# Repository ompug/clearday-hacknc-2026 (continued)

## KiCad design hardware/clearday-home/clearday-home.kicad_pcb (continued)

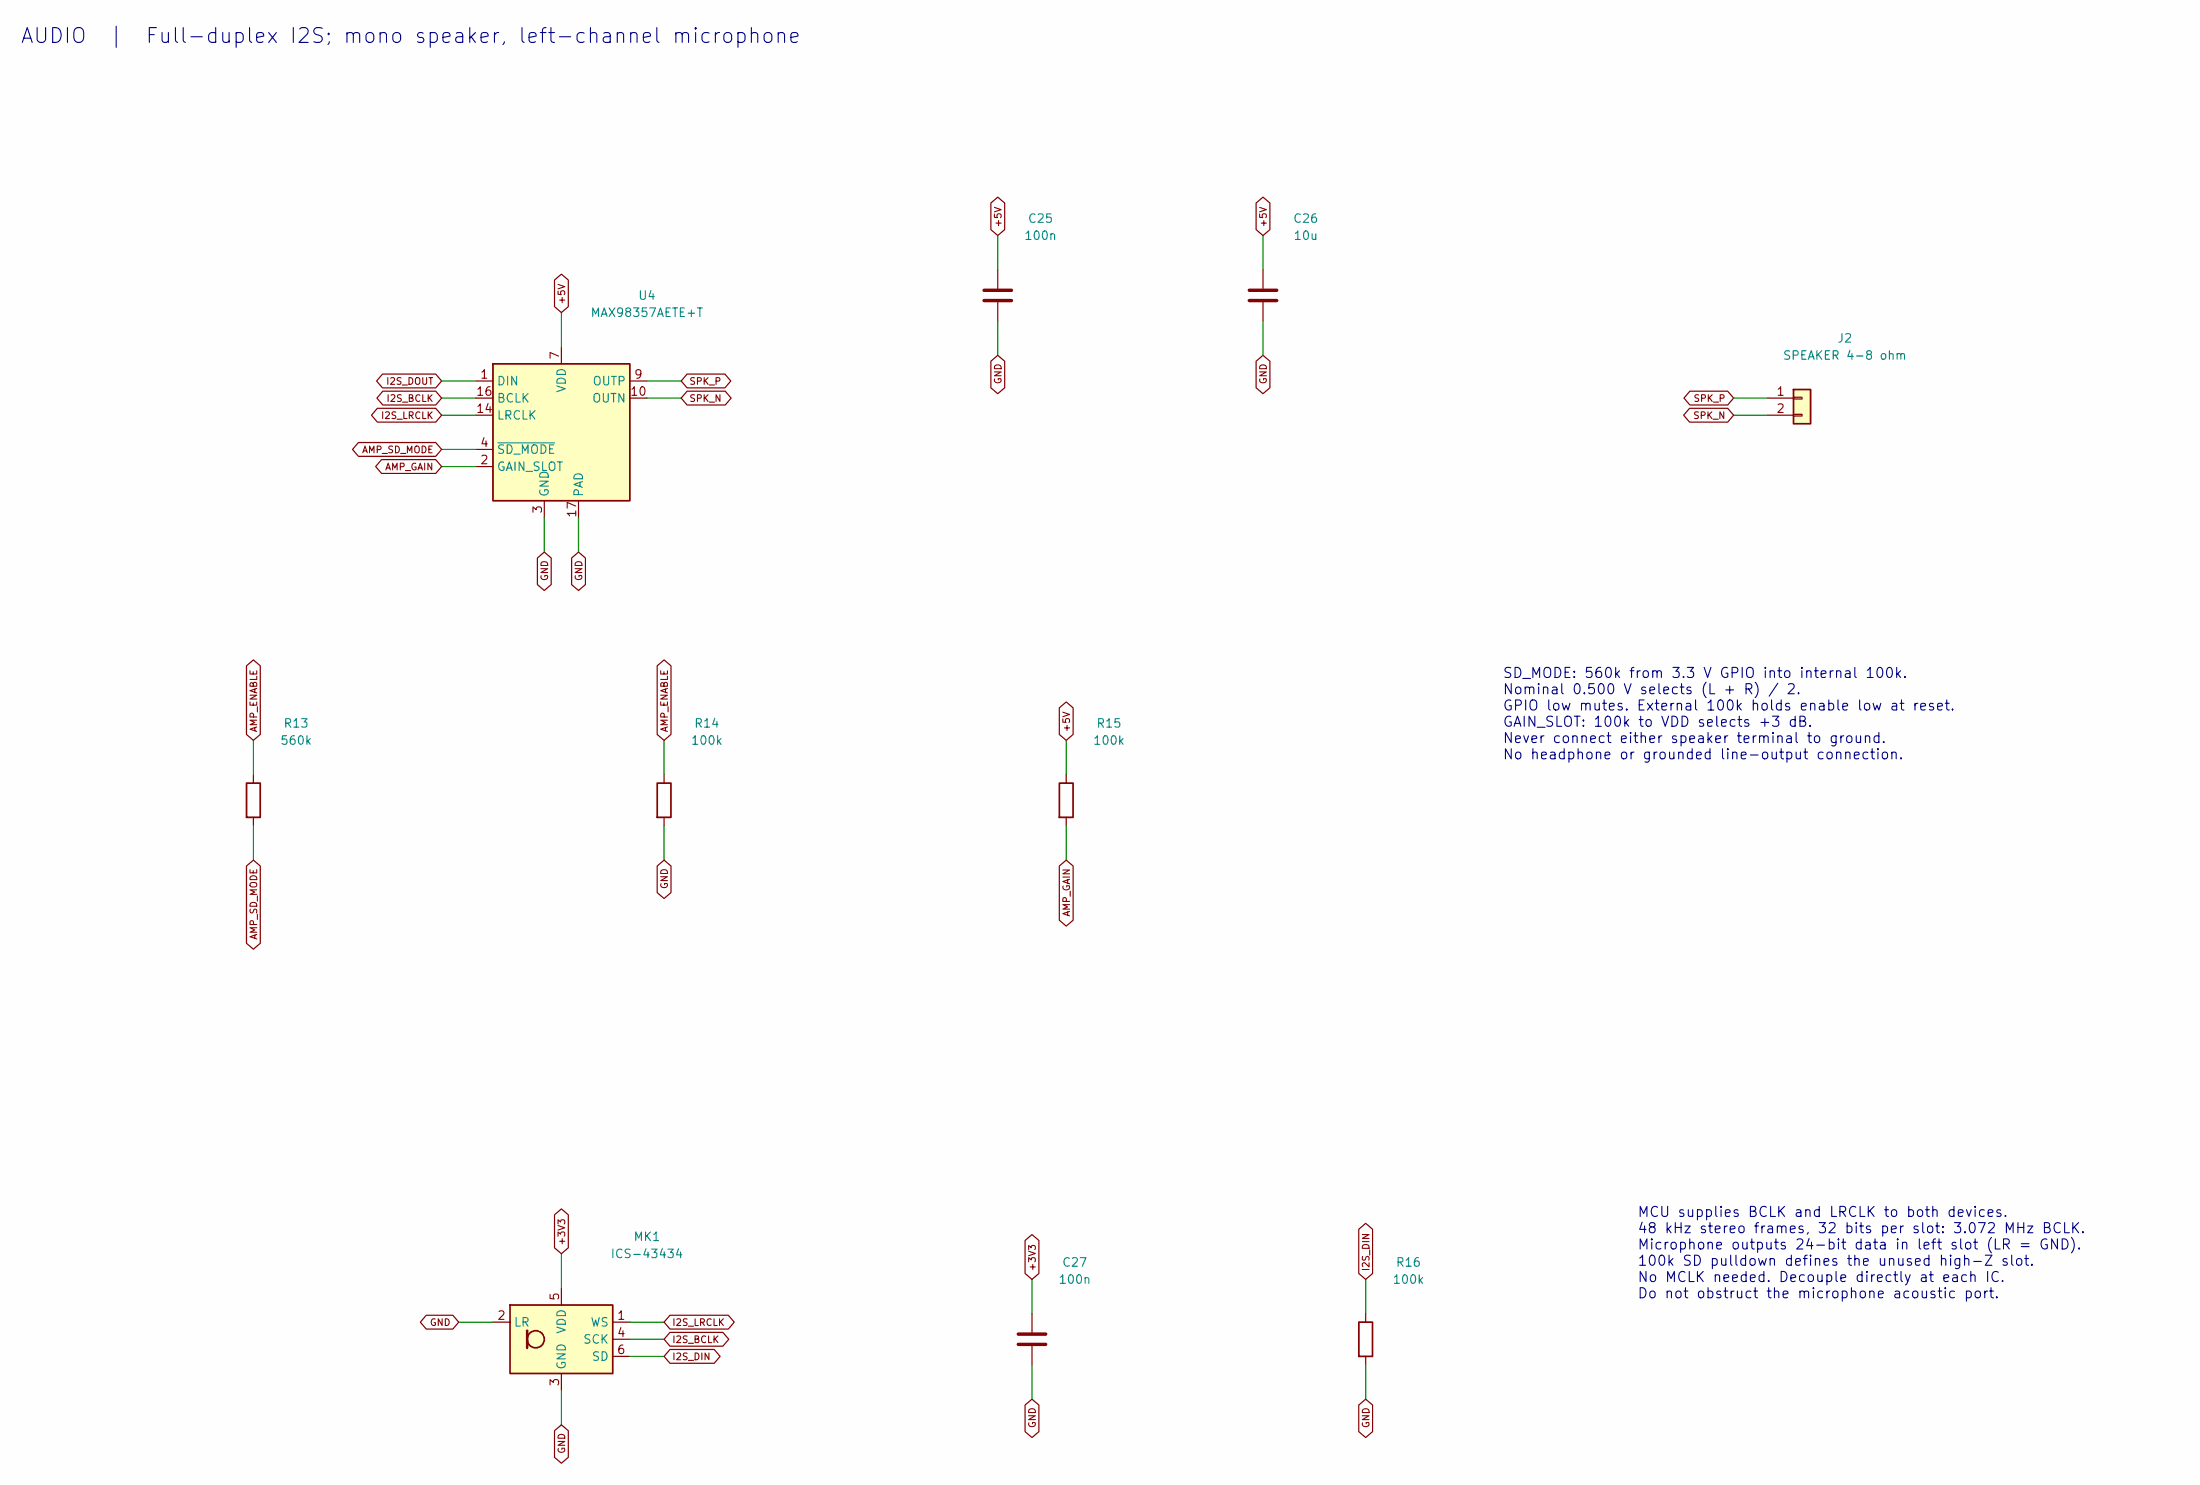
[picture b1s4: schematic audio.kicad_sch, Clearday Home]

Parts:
C25, C27: 100n; C_0603_1608Metric; MPN GRM188R71C104KA01D
C26: 10u; C_0805_2012Metric; MPN GRM21BR61A106KE19L
J2: SPEAKER 4-8 ohm; JST_PH_B2B-PH-K_1x02_P2.00mm_Vertical; MPN B2B-PH-K-S(LF)(SN)
MK1: ICS-43434; InvenSense_ICS-43434-6_3.5x2.65mm; MPN ICS-43434
R13: 560k; R_0603_1608Metric; MPN RC0603FR-07560KL
R14, R15, R16: 100k; R_0603_1608Metric; MPN RC0603FR-07100KL
U4: MAX98357AETE+T; TQFN-16-1EP_3x3mm_P0.5mm_EP1.23x1.23mm; MPN MAX98357AETE+T

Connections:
+3V3: C27.1, MK1.5 (VDD); also elsewhere on the board
+5V: C25.1, C26.1, R15.1, U4.7 (VDD), U4.8 (VDD); also elsewhere on the board
AMP_ENABLE: R13.1, R14.1; also elsewhere on the board
AMP_GAIN: R15.2, U4.2 (GAIN_SLOT)
AMP_SD_MODE: R13.2, U4.4 (~SD_MODE)
GND: C25.2, C26.2, C27.2, MK1.2 (LR), MK1.3 (GND), R14.2, R16.2, U4.3 (GND), U4.11 (GND), U4.15 (GND), U4.17 (PAD); also elsewhere on the board
I2S_BCLK: MK1.4 (SCK), U4.16 (BCLK); also elsewhere on the board
I2S_DIN: MK1.6 (SD), R16.1; also elsewhere on the board
I2S_DOUT: U4.1 (DIN); also elsewhere on the board
I2S_LRCLK: MK1.1 (WS), U4.14 (LRCLK); also elsewhere on the board
SPK_N: J2.2, U4.10 (OUTN)
SPK_P: J2.1, U4.9 (OUTP)

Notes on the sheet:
AUDIO | Full-duplex I2S; mono speaker, left-channel microphone
SD_MODE: 560k from 3.3 V GPIO into internal 100k. Nominal 0.500 V selects (L + R) / 2. GPIO low mutes. External 100k holds enable low at reset. GAIN_SLOT: 100k to VDD selects +3 dB. Never connect either speaker terminal to ground. No headphone or grounded line-output connection.
MCU supplies BCLK and LRCLK to both devices. 48 kHz stereo frames, 32 bits per slot: 3.072 MHz BCLK. Microphone outputs 24-bit data in left slot (LR = GND). 100k SD pulldown defines the unused high-Z slot. No MCLK needed. Decouple directly at each IC. Do not obstruct the microphone acoustic port.

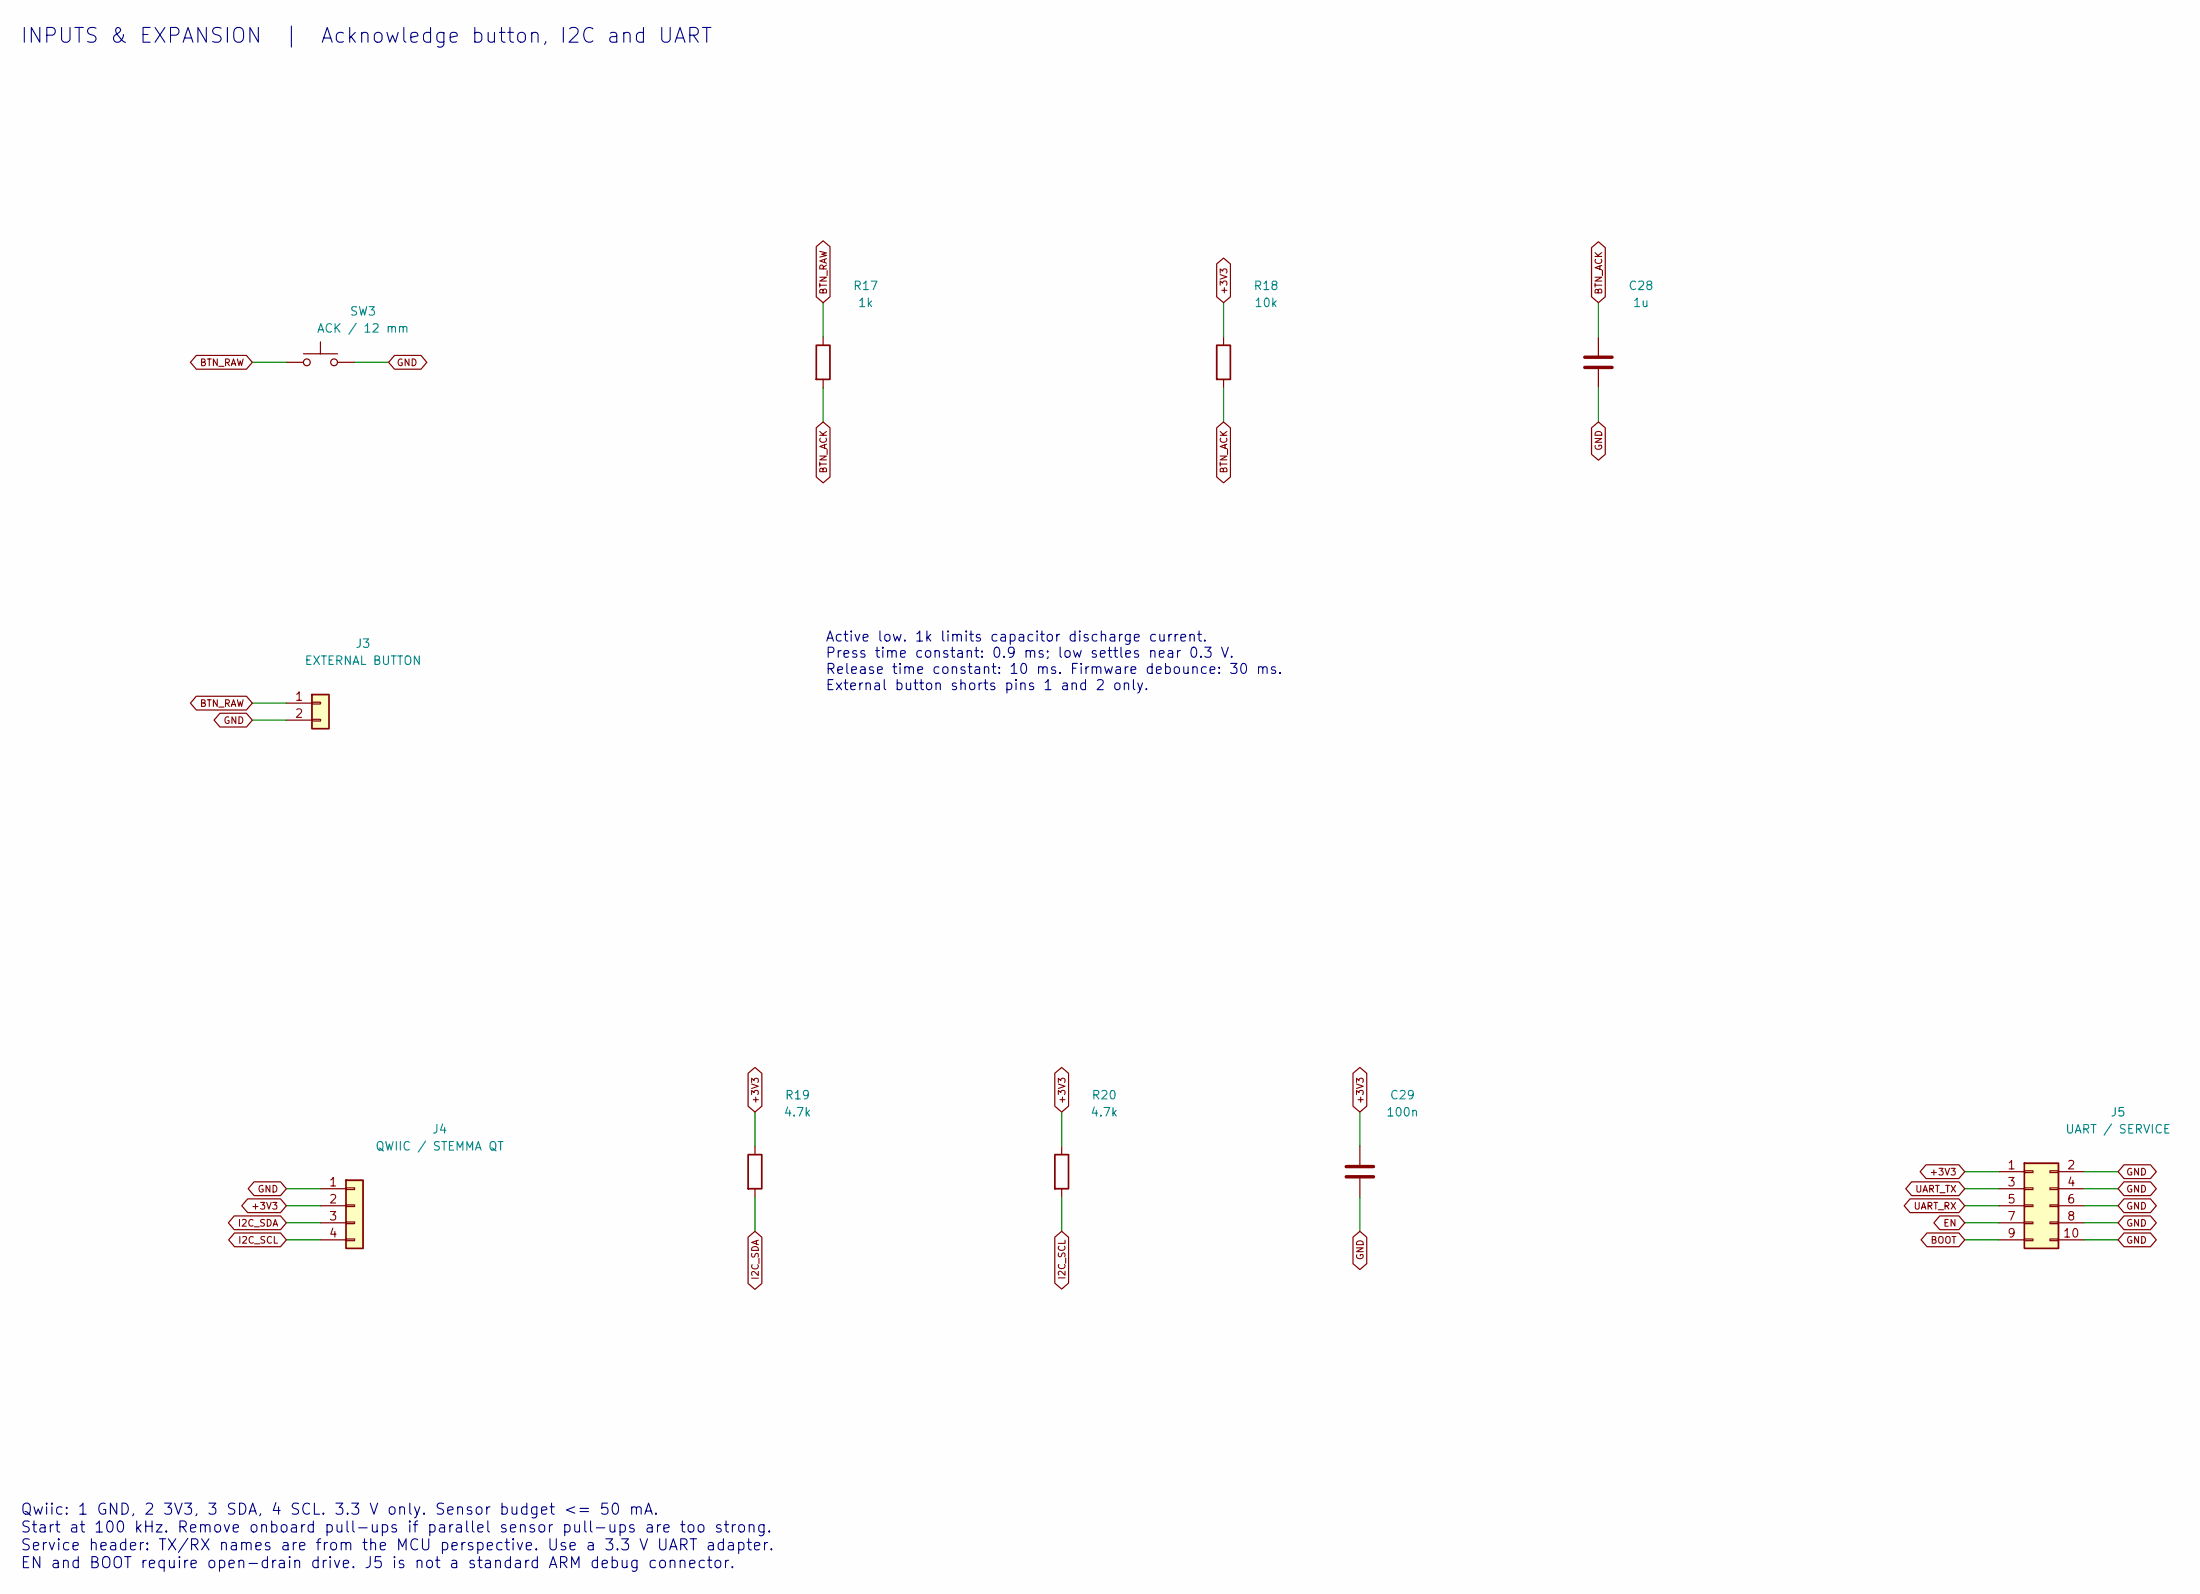
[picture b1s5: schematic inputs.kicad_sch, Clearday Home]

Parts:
C28: 1u; C_0603_1608Metric; MPN GRM188R61A105KA61D
C29: 100n; C_0603_1608Metric; MPN GRM188R71C104KA01D
J3: EXTERNAL BUTTON; JST_PH_B2B-PH-K_1x02_P2.00mm_Vertical; MPN B2B-PH-K-S(LF)(SN)
J4: QWIIC / STEMMA QT; JST_SH_BM04B-SRSS-TB_1x04-1MP_P1.00mm_Vertical; MPN BM04B-SRSS-TB(LF)(SN)
J5: UART / SERVICE; PinHeader_2x05_P1.27mm_Vertical; MPN FTSH-105-01-L-D
R17: 1k; R_0603_1608Metric; MPN RC0603FR-071KL
R18: 10k; R_0603_1608Metric; MPN RC0603FR-0710KL
R19, R20: 4.7k; R_0603_1608Metric; MPN RC0603FR-074K7L
SW3: ACK / 12 mm; SW_PUSH-12mm; MPN B3F-4050

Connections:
+3V3: C29.1, J4.2, J5.1, R18.1, R19.1, R20.1; also elsewhere on the board
BOOT: J5.9; also elsewhere on the board
BTN_ACK: C28.1, R17.2, R18.2; also elsewhere on the board
BTN_RAW: J3.1, R17.1, SW3.1
EN: J5.7; also elsewhere on the board
GND: C28.2, C29.2, J3.2, J4.1, J5.2, J5.4, J5.6, J5.8, J5.10, SW3.2; also elsewhere on the board
I2C_SCL: J4.4, R20.2; also elsewhere on the board
I2C_SDA: J4.3, R19.2; also elsewhere on the board
UART_RX: J5.5; also elsewhere on the board
UART_TX: J5.3; also elsewhere on the board

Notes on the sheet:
INPUTS & EXPANSION | Acknowledge button, I2C and UART
Active low. 1k limits capacitor discharge current. Press time constant: 0.9 ms; low settles near 0.3 V. Release time constant: 10 ms. Firmware debounce: 30 ms. External button shorts pins 1 and 2 only.
Qwiic: 1 GND, 2 3V3, 3 SDA, 4 SCL. 3.3 V only. Sensor budget <= 50 mA. Start at 100 kHz. Remove onboard pull-ups if parallel sensor pull-ups are too strong. Service header: TX/RX names are from the MCU perspective. Use a 3.3 V UART adapter. EN and BOOT require open-drain drive. J5 is not a standard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

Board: 2 copper layers, 78 parts (54 on the bottom side), 49 nets, no tracks yet.

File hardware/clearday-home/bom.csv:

References,Quantity,Value,MPN,Footprint,Manufacturer,Notes
J1,1,USB-C / USB 2.0,USB4105-GF-A,Connector_USB:USB_C_Receptacle_GCT_USB4105-xx-A_16P_TopMnt_Horizontal,GCT,
"R1, R2",2,5.1k,RC0603FR-075K1L,Resistor_SMD:R_0603_1608Metric,Yageo,"1%, 0.1 W"
U2,1,USBLC6-2SC6,USBLC6-2SC6,Package_TO_SOT_SMD:SOT-23-6,STMicroelectronics,
"C1, C7, C12, C13, C14, C15, C16, C17, C18, C19, C20, C21, C22, C23, C24, C25, C27, C29",18,100n,GRM188R71C104KA01D,Capacitor_SMD:C_0603_1608Metric,Murata,16 V X7R
"R3, R4",2,22,RC0603FR-0722RL,Resistor_SMD:R_0603_1608Metric,Yageo,"1%, 0.1 W"
F1,1,2 A hold / 6 V,1206L200/6,Fuse:Fuse_1206_3216Metric,Littelfuse,PTC; derate hold current with temperature
"C2, C8, C9, C28",4,1u,GRM188R61A105KA61D,Capacitor_SMD:C_0603_1608Metric,Murata,10 V X5R
U3,1,AP7361C-33E / 1 A,AP7361C-33E-13,Package_TO_SOT_SMD:SOT-223-3_TabPin2,Diodes Incorporated,SOT-223 tab is GND; thermal copper required
"C3, C6, C26",3,10u,GRM21BR61A106KE19L,Capacitor_SMD:C_0805_2012Metric,Murata,10 V X5R
"R5, R17",2,1k,RC0603FR-071KL,Resistor_SMD:R_0603_1608Metric,Yageo,"1%, 0.1 W"
D1,1,POWER green,LTST-C190KGKT,LED_SMD:LED_0603_1608Metric,Lite-On,
"R6, R7, R8, R9, R18",5,10k,RC0603FR-0710KL,Resistor_SMD:R_0603_1608Metric,Yageo,"1%, 0.1 W"
"C4, C5, C10",3,10n,GRM188R71H103KA01D,Capacitor_SMD:C_0603_1608Metric,Murata,50 V X7R
U1,1,ESP32-S3-WROOM-1-N8R8,ESP32-S3-WROOM-1-N8R8,RF_Module:ESP32-S3-WROOM-1,Espressif Systems,"8 MB flash, 8 MB octal PSRAM; IO35/36/37 reserved"
SW1,1,RESET,B3U-1000P,Button_Switch_SMD:SW_SPST_B3U-1000P,Omron,
SW2,1,BOOT,B3U-1000P,Button_Switch_SMD:SW_SPST_B3U-1000P,Omron,
U6,1,TPS22918DBVR,TPS22918DBVR,Package_TO_SOT_SMD:SOT-23-6,Texas Instruments,QOD intentionally open for 1000 uF load
"R10, R12, R14, R15, R16",5,100k,RC0603FR-07100KL,Resistor_SMD:R_0603_1608Metric,Yageo,"1%, 0.1 W"
C11,1,1000u,EEU-FR1A102,Capacitor_THT:CP_Radial_D10.0mm_P5.00mm,Panasonic,"10 V, D10 x H16 mm"
U5,1,74AHCT1G125,SN74AHCT1G125DBVR,Package_TO_SOT_SMD:SOT-23-5,Texas Instruments,
R11,1,330,RC0603FR-07330RL,Resistor_SMD:R_0603_1608Metric,Yageo,"1%, 0.1 W"
"D2, D3, D4, D5, D6, D7, D8, D9, D10, D11, D12, D13",12,WS2812B-V5,WS2812B-V5/W,LED_SMD:LED_WS2812B_PLCC4_5.0x5.0mm_P3.2mm,Worldsemi,
U4,1,MAX98357AETE+T,MAX98357AETE+T,Package_DFN_QFN:TQFN-16-1EP_3x3mm_P0.5mm_EP1.23x1.23mm,Analog Devices,"Exposed pad to GND; BTL outputs, neither speaker wire is ground"
R13,1,560k,RC0603FR-07560KL,Resistor_SMD:R_0603_1608Metric,Yageo,"1%, 0.1 W"
J2,1,SPEAKER 4-8 ohm,B2B-PH-K-S(LF)(SN),Connector_JST:JST_PH_B2B-PH-K_1x02_P2.00mm_Vertical,JST,Use approximately 3 W speaker; floating BTL connection
MK1,1,ICS-43434,ICS-43434,Sensor_Audio:InvenSense_ICS-43434-6_3.5x2.65mm,TDK InvenSense,Bottom port: footprint acoustic hole must remain open
SW3,1,ACK / 12 mm,B3F-4050,Button_Switch_THT:SW_PUSH-12mm,Omron,Rear-facing 12 mm tactile switch
J3,1,EXTERNAL BUTTON,B2B-PH-K-S(LF)(SN),Connector_JST:JST_PH_B2B-PH-K_1x02_P2.00mm_Vertical,JST,Optional passive arcade switch; no external voltage
J4,1,QWIIC / STEMMA QT,BM04B-SRSS-TB(LF)(SN),Connector_JST:JST_SH_BM04B-SRSS-TB_1x04-1MP_P1.00mm_Vertical,JST,
"R19, R20",2,4.7k,RC0603FR-074K7L,Resistor_SMD:R_0603_1608Metric,Yageo,"1%, 0.1 W"
J5,1,UART / SERVICE,FTSH-105-01-L-D,Connector_PinHeader_1.27mm:PinHeader_2x05_P1.27mm_Vertical,Samtec,"Custom UART pinout, not ARM SWD; 3.3 V is reference, do not power from debugger"
